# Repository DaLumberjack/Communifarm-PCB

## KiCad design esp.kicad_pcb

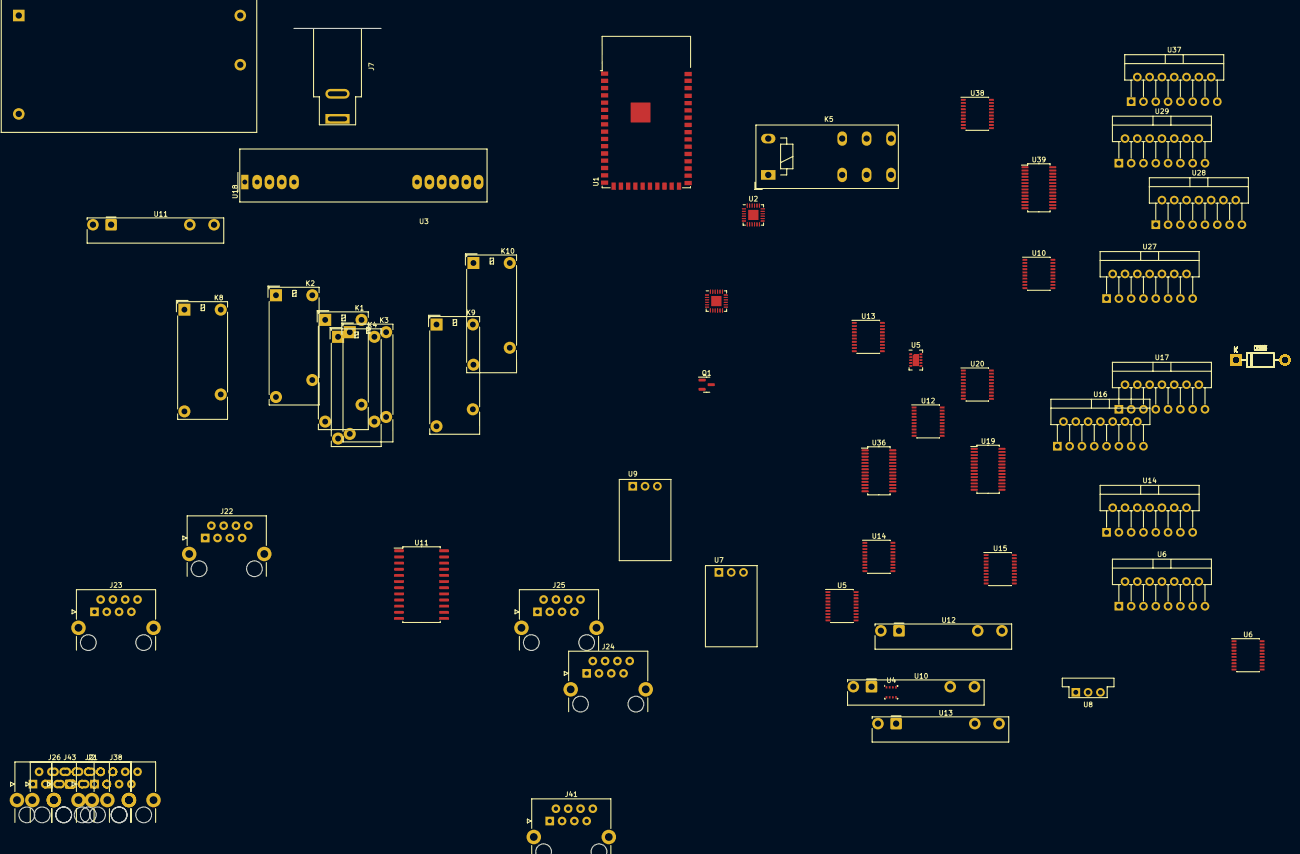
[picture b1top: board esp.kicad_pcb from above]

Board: 2 copper layers, 95 parts (0 on the bottom side), 115 nets, no tracks yet.

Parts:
D1, D2, D3, D4, D5, D6, D7, D8, D9, D10, D11, D12, D13, D14, D15, D16, D17, D18, D19, D20, D21, D22, D23, D24, D25, D26, D27, D28, D29, D30, D31, D32, D33, D34, D35, D36, D37, D38, D39, D40: 1N4001; D_DO-41_SOD81_P10.16mm_Horizontal
J2, J21, J22, J23, J24, J25, J26, J38, J41, J43: 8P8C_Shielded; RJ45_HALO_HFJ11-x2450HRL_Horizontal
J7: Barrel_Jack_MountingPin; BarrelJack_SwitchcraftConxall_RAPC10U_Horizontal
K1, K2, K3, K4, K8, K9, K10: RT314A24; Relay_1P1T_NO_10x24x18.8mm_Panasonic_ADW11xxxxW_THT
K5: RT314A24; Relay_SPDT_Schrack-RT1-16A-FormC_RM5mm
PS1: RAC20-24SK; Converter_ACDC_Recom_RAC20-xxSK_THT
Q1: BSS138; SOT-23
U1: ESP32-S2-WROVER
U2, U3: TCA9548ARGER; Texas_RGE0024C_EP2.1x2.1mm
U4: BME280; Bosch_LGA-8_2.5x2.5mm_P0.65mm_ClockwisePinNumbering
U5, U6, U10#2, U12#2, U13#2, U14#2, U15, U20, U38: PCF8574ATS; SSOP-20_4.4x6.5mm_P0.65mm
U5#2: CCS811; AMS_LGA-10-1EP_2.7x4mm_P0.6mm
U6#2, U14, U16, U17, U27, U28, U29, U37: L298N; TO-220-15_P2.54x2.54mm_StaggerOdd_Lead4.58mm_Vertical
U7: OKI-78SR-12_1.0-W36H-C; Converter_DCDC_Murata_OKI-78SR_Horizontal
U8: OKI-78SR-5_1.5-W36-C; Converter_DCDC_Murata_OKI-78SR_Vertical
U9: OKI-78SR-3.3_1.5-W36H-C; Converter_DCDC_Murata_OKI-78SR_Horizontal
U10, U12: 34.81-9024; Finder_34.81
U11, U13: 34.81-8240; Finder_34.81
U11#2: PCA9548ADW; SOIC-24W_7.5x15.4mm_P1.27mm
U18: NID30S48-24; Converter_DCDC_MeanWell_NID30_THT
U19, U36, U39: PCA9685PW; TSSOP-28_4.4x9.7mm_P0.65mm

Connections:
+3.3V: J26.1, J26.4, J41.1, J41.4, U5.15 (VSS), U12#2.15 (VSS)
+12V: D1.1 (K), D2.1 (K), D3.1 (K), D4.1 (K), D9.1 (K), D11.1 (K), D13.1 (K), D15.1 (K), D17.1 (K), D19.1 (K), D21.1 (K), D23.1 (K), D25.1 (K), D27.1 (K), D29.1 (K), D31.1 (K), D33.1 (K), D35.1 (K), D37.1 (K), D39.1 (K), K5.A2, U27.4 (Vs)
GND: D5.2 (A), D6.2 (A), D7.2 (A), D8.2 (A), D10.2 (A), D12.2 (A), D14.2 (A), D16.2 (A), D18.2 (A), D20.2 (A), D22.2 (A), D24.2 (A), D26.2 (A), D28.2 (A), D30.2 (A), D32.2 (A), D34.2 (A), D36.2 (A), D38.2 (A), D40.2 (A), J26.3, J26.6, J41.3, J41.6, K5.11, U5.5 (VDD), U5.6 (A0), U5.9 (A2), U5#2.11 (GND), U6.5 (VDD), U6#2.1 (SENSE_A), U6#2.4 (Vs), U6#2.8 (GND), U12#2.5 (VDD), U14.1 (SENSE_A), U14.4 (Vs), U14.8 (GND), U14#2.5 (VDD), U15.6 (A0), U15.15 (VSS), U16.1 (SENSE_A), U16.4 (Vs), U16.8 (GND), U17.1 (SENSE_A), U17.4 (Vs), U17.8 (GND), U19.1 (A0), U19.14 (VSS), U20.6 (A0), U20.7 (A1), U20.15 (VSS), U27.1 (SENSE_A), U27.8 (GND)
IN7: U5.19 (P6), U5.20 (P7)
unnamed: U7.1 (IN), U8.1 (IN), U9.1 (IN)
unnamed: J7.2, PS1.4 (-Vout)
unnamed: D1.2 (A), D6.1 (K), U27.13 (OUT3)
unnamed: D2.2 (A), D5.1 (K), U27.14 (OUT4)
unnamed: D3.2 (A), D7.1 (K), U27.3 (OUT2)
unnamed: D4.2 (A), D8.1 (K), U27.2 (OUT1)
unnamed: D9.2 (A), D10.1 (K), U14.14 (OUT4)
unnamed: D11.2 (A), D12.1 (K), U14.13 (OUT3)
unnamed: D13.2 (A), D14.1 (K), U14.3 (OUT2)
unnamed: D15.2 (A), D16.1 (K), U14.2 (OUT1)
unnamed: D17.2 (A), D18.1 (K), U6#2.14 (OUT4)
unnamed: D19.2 (A), D20.1 (K), U6#2.13 (OUT3)
unnamed: D21.2 (A), D22.1 (K), U6#2.3 (OUT2)
unnamed: D23.2 (A), D24.1 (K), U6#2.2 (OUT1)
unnamed: D25.2 (A), D26.1 (K), U16.14 (OUT4)
unnamed: D27.2 (A), D28.1 (K), U17.14 (OUT4)
unnamed: D29.2 (A), D30.1 (K), U16.13 (OUT3)
unnamed: D31.2 (A), D32.1 (K), U17.13 (OUT3)
unnamed: D33.2 (A), D34.1 (K), U16.3 (OUT2)
unnamed: D35.2 (A), D36.1 (K), U17.3 (OUT2)
unnamed: D37.2 (A), D38.1 (K), U16.2 (OUT1)
unnamed: D39.2 (A), D40.1 (K), U17.2 (OUT1)
unnamed: U11.11, U18.7 (Vin), U18.8 (Vin)
unnamed: U18.1 (Vout), U18.2 (Vout), U18.3 (Vout), U18.4 (Vout)
unnamed: J26.2, J26.5, J26.7, J26.8
unnamed: J41.2, J41.5, J41.7, J41.8
unnamed: Q1.2 (S), U36.17 (LED10)
unnamed: U1.1 (GND), U1.26 (GND), U1.42 (GND), U1.43 (GND)
unnamed: U1.19 (IO16), U3.20 (SDA), U14#2.2 (SCL)
unnamed: U1.20 (IO17), U3.19 (SCL), U6.4 (SDA)
unnamed: U1.34 (IO40), U2.20 (SDA)
unnamed: U1.35 (IO41), U2.19 (SCL)
unnamed: U3.22 (A0), U3.23 (A1)
unnamed: U6.12 (P2), U11.A1
unnamed: U6.16 (P4), U10.A1
unnamed: U10#2.10 (P0), U27.5 (IN1)
unnamed: U10#2.11 (P1), U27.7 (IN2)
unnamed: U10#2.12 (P2), U27.10 (IN3)
unnamed: U10#2.14 (P3), U27.12 (IN4)
unnamed: U10#2.16 (P4), U28.5 (IN1)
unnamed: U10#2.17 (P5), U28.7 (IN2)
unnamed: U10#2.19 (P6), U28.10 (IN3)
unnamed: U10#2.20 (P7), U28.12 (IN4)
unnamed: J22.2, U11#2.5 (SC0)
unnamed: J22.6, U11#2.7 (SC1)
unnamed: J23.2, U11#2.9 (SC2)
unnamed: J23.6, U11#2.11 (SC3)
unnamed: J24.2, U11#2.14 (SC4)
unnamed: J24.6, U11#2.16 (SC5)
unnamed: J25.2, U11#2.18 (SC6)
unnamed: J25.6, U11#2.20 (SC7)
unnamed: J22.3, U11#2.4 (SD0)
unnamed: J22.7, U11#2.6 (SD1)
unnamed: J23.3, U11#2.8 (SD2)
unnamed: J23.7, U11#2.10 (SD3)
unnamed: J24.3, U11#2.13 (SD4)
unnamed: J24.7, U11#2.15 (SD5)
unnamed: J25.3, U11#2.17 (SD6)
unnamed: J25.7, U11#2.19 (SD7)
unnamed: U13.A1, U14#2.12 (P2)
unnamed: U12.A1, U14#2.16 (P4)
unnamed: U3.2 (SC0), U15.2 (SCL)
unnamed: U3.1 (SD0), U15.4 (SDA)
unnamed: U18.5 (COM), U18.6 (COM)
unnamed: U3.4 (SC1), U19.26 (SCL)
unnamed: U3.3 (SD1), U19.27 (SDA)
unnamed: U3.6 (SC2), U20.2 (SCL)
unnamed: U3.5 (SD2), U20.4 (SDA)
unnamed: U27.6 (EnA), U39.6 (LED0)
unnamed: U27.11 (EnB), U39.7 (LED1)
unnamed: U28.6 (EnA), U39.8 (LED2)
unnamed: U28.11 (EnB), U39.9 (LED3)
unnamed: U29.6 (EnA), U39.10 (LED4)
unnamed: U29.11 (EnB), U39.11 (LED5)
unnamed: U29.5 (IN1), U38.10 (P0)
unnamed: U29.7 (IN2), U38.11 (P1)
unnamed: U29.10 (IN3), U38.12 (P2)
unnamed: U29.12 (IN4), U38.14 (P3)
unnamed: U37.6 (EnA), U39.12 (LED6)
unnamed: U37.11 (EnB), U39.13 (LED7)
unnamed: U37.5 (IN1), U38.16 (P4)
unnamed: U37.7 (IN2), U38.17 (P5)
unnamed: U37.10 (IN3), U38.19 (P6)
unnamed: U37.12 (IN4), U38.20 (P7)
PCA_0_LED_0: U14.6 (EnA), U19.6 (LED0)
PCA_0_LED_1: U14.11 (EnB), U19.7 (LED1)
PCA_0_LED_2: U6#2.6 (EnA), U19.8 (LED2)
PCA_0_LED_3: U6#2.11 (EnB), U19.9 (LED3)
PCA_0_LED_4: U17.6 (EnA), U19.10 (LED4)
PCA_0_LED_5: U17.11 (EnB), U19.11 (LED5)
PCA_0_LED_6: U16.6 (EnA), U19.12 (LED6)
PCA_0_LED_7: U16.11 (EnB), U19.13 (LED7)
PCF_0_GPIO_0: U14.5 (IN1), U15.10 (P0)
PCF_0_GPIO_1: U14.7 (IN2), U15.11 (P1)
PCF_0_GPIO_2: U14.10 (IN3), U15.12 (P2)
PCF_0_GPIO_3: U14.12 (IN4), U15.14 (P3)
PCF_0_GPIO_4: U6#2.5 (IN1), U15.16 (P4)
PCF_0_GPIO_5: U6#2.7 (IN2), U15.17 (P5)
PCF_0_GPIO_6: U6#2.10 (IN3), U15.19 (P6)
PCF_0_GPIO_7: U6#2.12 (IN4), U15.20 (P7)
PCF_20_GPIO_0: U17.5 (IN1), U20.10 (P0)
PCF_20_GPIO_1: U17.7 (IN2), U20.11 (P1)
PCF_20_GPIO_2: U17.10 (IN3), U20.12 (P2)
PCF_20_GPIO_3: U17.12 (IN4), U20.14 (P3)
PCF_20_GPIO_4: U16.5 (IN1), U20.16 (P4)
PCF_20_GPIO_5: U16.7 (IN2), U20.17 (P5)
PCF_20_GPIO_6: U16.10 (IN3), U20.19 (P6)
PCF_20_GPIO_7: U16.12 (IN4), U20.20 (P7)
TCA_2_SC7: U3.17 (SC7), U5.2 (SCL)
TCA_2_SD7: J38.8, J43.8, U3.16 (SD7), U5.4 (SDA)
VCC: U6#2.9 (Vss), U14.9 (Vss), U15.5 (VDD), U16.9 (Vss), U17.9 (Vss), U19.28 (VDD), U20.5 (VDD)

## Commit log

2024-10-12 added ac/dc plug secondary battery with down
2024-10-12 added some sheets for detailed view
2024-10-12 barrel jack multiple versions, should be turned into branches
2024-10-12 some additions to barrel jack and its layout
2024-10-12 motor layout
2024-10-12 placeholders for ethernet and relay inputs
2024-10-12 i2c ethernet with POE
2024-10-12 dallas temp sensors
2024-10-12 some relay adjustments
2024-10-12 talk with casey movin
2024-10-13 add level converter to be compatible with high volt relay
2024-10-13 added layout from online made room for full 41f switch
2024-10-13 resistors for teams
2024-10-13 larger file for main layout
2024-10-14 main sheet barrel connector
2024-10-14 add some relay stuff, not complete
2024-10-14 relay from SolderedElectronics/2-channel-relay-board-hardware-design
2024-10-14 relay from SolderedElectronics/2-channel-relay-board-hardware-design added clean up and connections to gpio expander todo: check to see if this works with 3.3 v or put a level shifter
2024-10-14 evening cleanup
2024-10-15 global labels for simple viewing
2024-10-16 PCB can be built, naming issues
2024-10-16 slimmed down and spread out pcb
2024-10-19 working scematic with seperated layout
